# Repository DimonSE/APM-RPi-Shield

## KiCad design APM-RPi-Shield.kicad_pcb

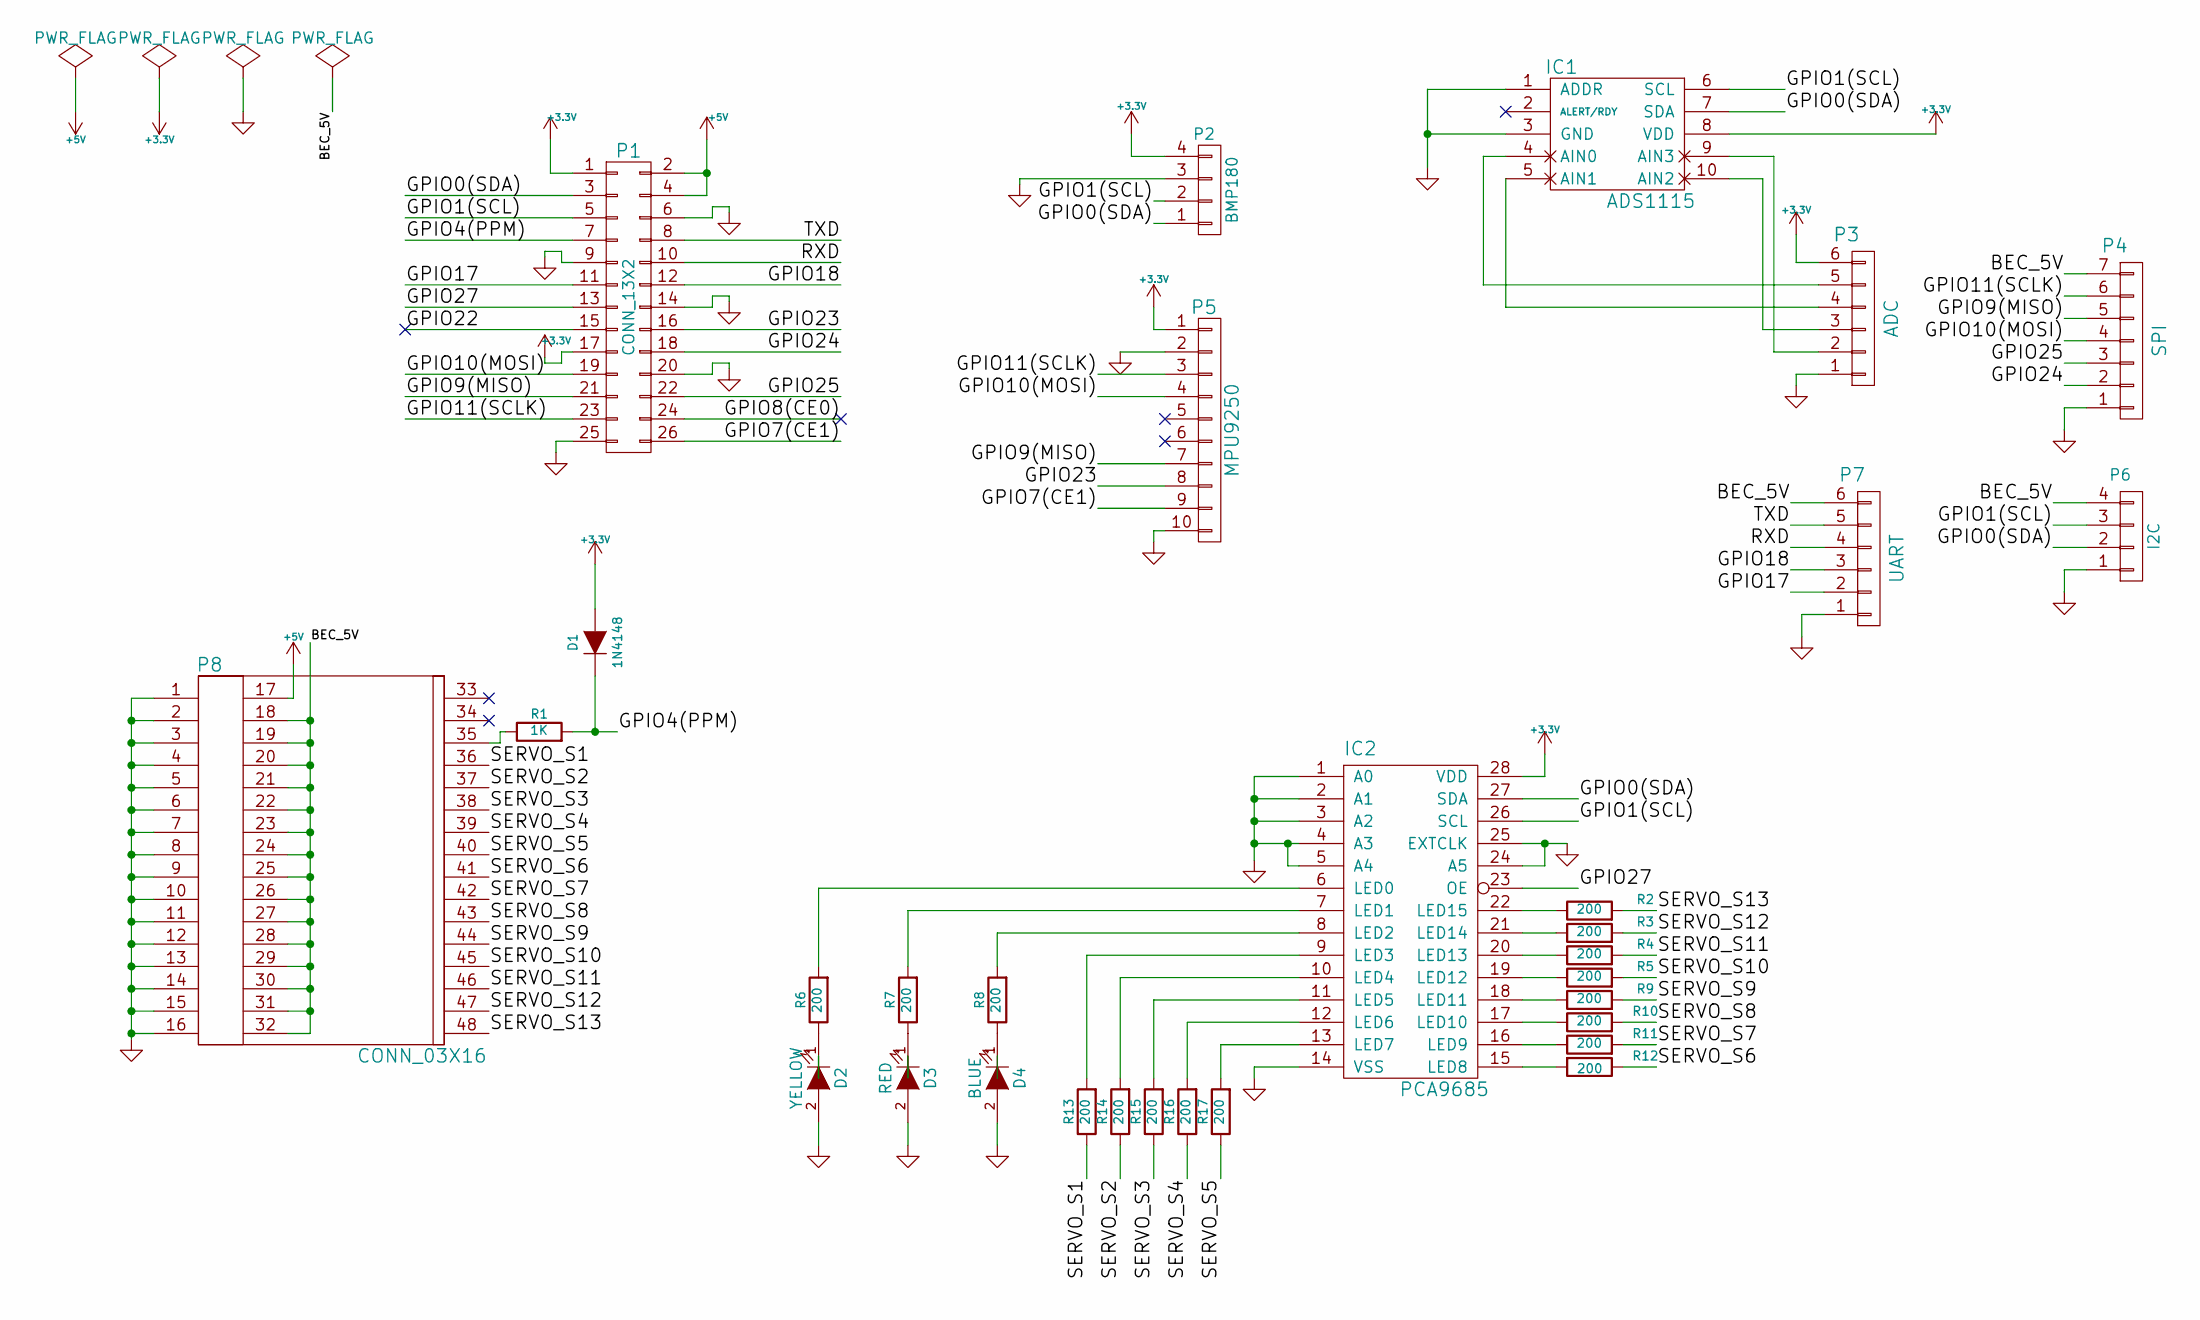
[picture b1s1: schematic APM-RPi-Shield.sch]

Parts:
D1: 1N4148; SOD-123
D2: YELLOW; LED-3MM
D3: RED; LED-3MM
D4: BLUE; LED-3MM
IC1: ADS1115; MSOP-10-1EP_3x3mm_Pitch0.5mm
IC2: PCA9685; TSSOP-28_4.4x9.7mm_Pitch0.65mm
P1: CONN_13X2; Pin_Header_Straight_2x13
P2: BMP180; Pin_Header_Straight_1x04
P3: ADC; Connector_Molex_PicoBlade_53398-0671
P4: SPI; Connector_Molex_PicoBlade_53398-0771
P5: MPU9250; Pin_Header_Straight_1x10
P6: I2C; Connector_Molex_PicoBlade_53398-0471
P7: UART; Connector_Molex_PicoBlade_53398-0671
P8: CONN_03X16; Pin_Header_Straight_3x16
R1: 1K; R_0805
R2, R3, R4, R5, R6, R7, R8, R9, R10, R11, R12, R13, R14, R15, R16, R17: 200; R_0805

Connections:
+3V3: D1.2 (A), IC1.8 (VDD), IC2.28 (VDD), P1.1, P1.17, P2.4, P3.6, P5.1
+5V: P1.2, P1.4, P8.17
/BEC_5V: P4.7, P6.4, P7.6, P8.18, P8.19, P8.20, P8.21, P8.22, P8.23, P8.24, P8.25, P8.26, P8.27, P8.28, P8.29, P8.30, P8.31, P8.32
/GPIO0(SDA): IC1.7 (SDA), IC2.27 (SDA), P1.3, P2.1, P6.2
/GPIO1(SCL): IC1.6 (SCL), IC2.26 (SCL), P1.5, P2.2, P6.3
/GPIO4(PPM): D1.1 (K), P1.7, R1.2
/GPIO7(CE1): P1.26, P5.9
/GPIO8(CE0): P1.24
/GPIO9(MISO): P1.21, P4.5, P5.7
/GPIO10(MOSI): P1.19, P4.4, P5.4
/GPIO11(SCLK): P1.23, P4.6, P5.3
/GPIO17: P1.11, P7.2
/GPIO18: P1.12, P7.3
/GPIO22: P1.15
/GPIO23: P1.16, P5.8
/GPIO24: P1.18, P4.2
/GPIO25: P1.22, P4.3
/GPIO27: IC2.23 (OE), P1.13
/RXD: P1.10, P7.4
/SERVO_S1: P8.36, R13.1
/SERVO_S2: P8.37, R14.1
/SERVO_S3: P8.38, R15.1
/SERVO_S4: P8.39, R16.1
/SERVO_S5: P8.40, R17.1
/SERVO_S6: P8.41, R12.1
/SERVO_S7: P8.42, R11.2
/SERVO_S8: P8.43, R10.2
/SERVO_S9: P8.44, R9.2
/SERVO_S10: P8.45, R5.2
/SERVO_S11: P8.46, R4.2
/SERVO_S12: P8.47, R3.2
/SERVO_S13: P8.48, R2.2
/TXD: P1.8, P7.5
GND: D2.2 (A), D3.2 (A), D4.2 (A), IC1.1 (ADDR), IC1.3 (GND), IC2.1 (A0), IC2.2 (A1), IC2.3 (A2), IC2.4 (A3), IC2.5 (A4), IC2.14 (VSS), IC2.24 (A5), IC2.25 (EXTCLK), P1.6, P1.9, P1.14, P1.20, P1.25, P2.3, P3.1, P4.1, P5.2, P5.10, P6.1, P7.1, P8.1, P8.2, P8.3, P8.4, P8.5, P8.6, P8.7, P8.8, P8.9, P8.10, P8.11, P8.12, P8.13, P8.14, P8.15, P8.16
unnamed: D2.1 (K), R6.1
unnamed: D3.1 (K), R7.1
unnamed: D4.1 (K), R8.1
unnamed: IC1.4 (AIN0), P3.5
unnamed: IC1.5 (AIN1), P3.4
unnamed: IC1.9 (AIN3), P3.2
unnamed: IC1.10 (AIN2), P3.3
unnamed: IC2.6 (LED0), R6.2
unnamed: IC2.7 (LED1), R7.2
unnamed: IC2.8 (LED2), R8.2
unnamed: IC2.9 (LED3), R13.2
unnamed: IC2.10 (LED4), R14.2
unnamed: IC2.11 (LED5), R15.2
unnamed: IC2.12 (LED6), R16.2
unnamed: IC2.13 (LED7), R17.2
unnamed: IC2.15 (LED8), R12.2
unnamed: IC2.16 (LED9), R11.1
unnamed: IC2.17 (LED10), R10.1
unnamed: IC2.18 (LED11), R9.1
unnamed: IC2.19 (LED12), R5.1
unnamed: IC2.20 (LED13), R4.1
unnamed: IC2.21 (LED14), R3.1
unnamed: IC2.22 (LED15), R2.1
unnamed: P8.35, R1.1

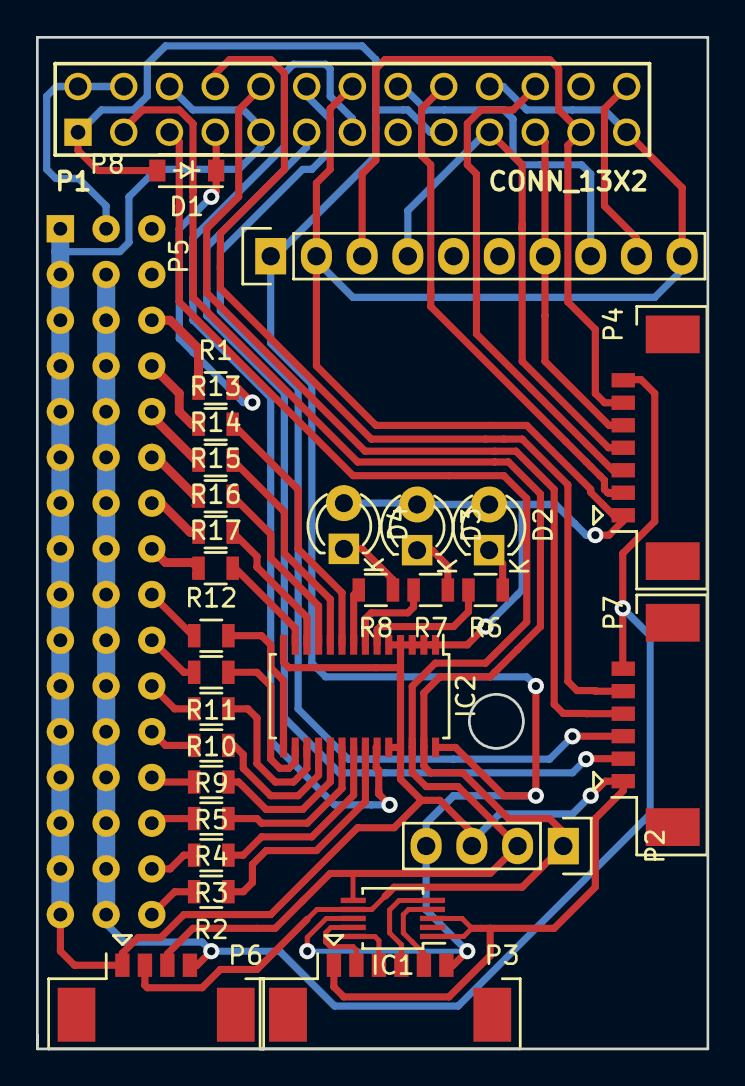
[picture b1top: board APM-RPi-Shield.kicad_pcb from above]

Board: 2 copper layers, 37.2 x 56.2 mm, 31 parts (0 on the bottom side), 56 nets.

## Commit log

2015-05-11 Add files.
2015-05-14 Change for 0.3mm row two-side
2015-05-14 Add pdf result. Small fixes
2015-05-31 fix on practic use
2015-05-31 update pdf files
2015-09-08 Add ublox GPS
